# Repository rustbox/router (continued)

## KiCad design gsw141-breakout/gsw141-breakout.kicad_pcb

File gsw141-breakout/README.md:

# GSW141 Switch Chip Breakout

## Different Arrangements of the GSW141 Breakout PCB?

### RJ45 Jacks

* Internal Magnetics | External Magnetics
* LEDs | No LEDs
* 1000 (or higher) Base-T
    * I think 1G capable means that there are 4 twisted pairs
* "Tab Up" | "Tab Down"
    * This means the tab on the cable. When tab is down, the cat-5 pins all in a row point "up",
and vise versa when tab is up.
    * The GSW141 chip routes traces best with "tab down"
    * "Tab up" + on the reverse side of the board is equivalent to "tab down"
* How many ports per part

### Internal Magnetics

Use `ARJM11C7-502-KB-EW2` on mouser
* Tab up, so would have to be placed on the reverse side of the PCB
* $3.09 @ 10

4x 1 unit = $12.36

=====================================================================

Use `TMJG26945AENL` on mouser, 1x2 port
* Tab down
* $11.34 per unit

2x 1 unit = $22.68

=====================================================================

Use `TMJG46945AENL` on mouser, 1x4 port
* Tab down
* $18.84 per unit

### External Magnetics

* Mouser `1149848` 4 port RJ45 w/ LEDs, $4.34 each
    * Tab up, so would have to be placed on PCB reverse side
* Mouser `LAN2VSOD48351C2` dual port magnetics chip, ~$2 each

1 @ 4.34 + 2 @ $2 = $8.34

====================================================================

* Mouser `1149854` 2 port RJ45 w/LEDs, $2.78 each
    * Tab up, reverse PCB side
* Mouser `LAN2VSOD48351C2` dual port magnetics chip, ~$2 each

2 @ 2.78 + 2 @ 2 = $9.56

# Board Questions
[ ] How should the 1000 Base T diff pairs be terminated into the magnetics?

# Board TODO

[x] 4 port RJ45 jack
[x] RJ45 LEDs
[x] Management Interface
    * SPI, etc
    * Pin headers
    [x] Strapping pins?
        * `206-125ST` on mouser
        * or `DS01C-254-L-09BE`
[x] GPIO Pins, header
[x] RGMII/SGMII over edge connctor
[x] RGMII/SGMII header
    [x] Remove these headers actually
[x] Power regulation, 3.3V, 1.1V
[x] Power jack (latching) and jack
    * Mouser `T6634ST` barrel connector
    * 5.5 mm (out) x 2.1 mm (in)
    * Out 0v, inside, pos
    * Barrel Jack: `694106301002` for above
[x] Clock input
    * `ECS-400-12-33B2Q-JES-TR3` on mouser
    * Clock circuit cap calculation comes from https://blog.adafruit.com/2012/01/24/choosing-the-right-crystal-and-caps-for-your-design/
    * CL = C1 * C2 / (C1 + C2) + Cstray
    * Cstray is ~3 pF
    * If C1 = C2 = C, and CL = 12 pF for the above crystal
    * so C = 2(CL - Cstray) => C = 18 pF
[x] Power switch, latching
    * Digikey `PB400EEQR1BLK` maybe?
[x] Reset Button
    * button `TS21-34-035-BK-160-SMT-TR` on mouser
[ ] Power indicator LEDs
[x] GSW Power Startup sequence
    * RC delay from 3.3 V into 1.1V enable
[ ] Make sure trace clearance is okay
[ ] Power off?
[x] Power Caps on GSW chip
[x] Blank R for RESREF and RCAL
[ ] Fix the RJ45 / magnetic pinout alignment so routing is easier
[ ] Diff Pairs that are off by more than 10s of mm should be length tuned
[ ] Empty Footprint for linear regulator(s)?
[ ] TI 1G checklist https://www.ti.com/lit/an/snla387/snla387.pdf?ts=1720391456901

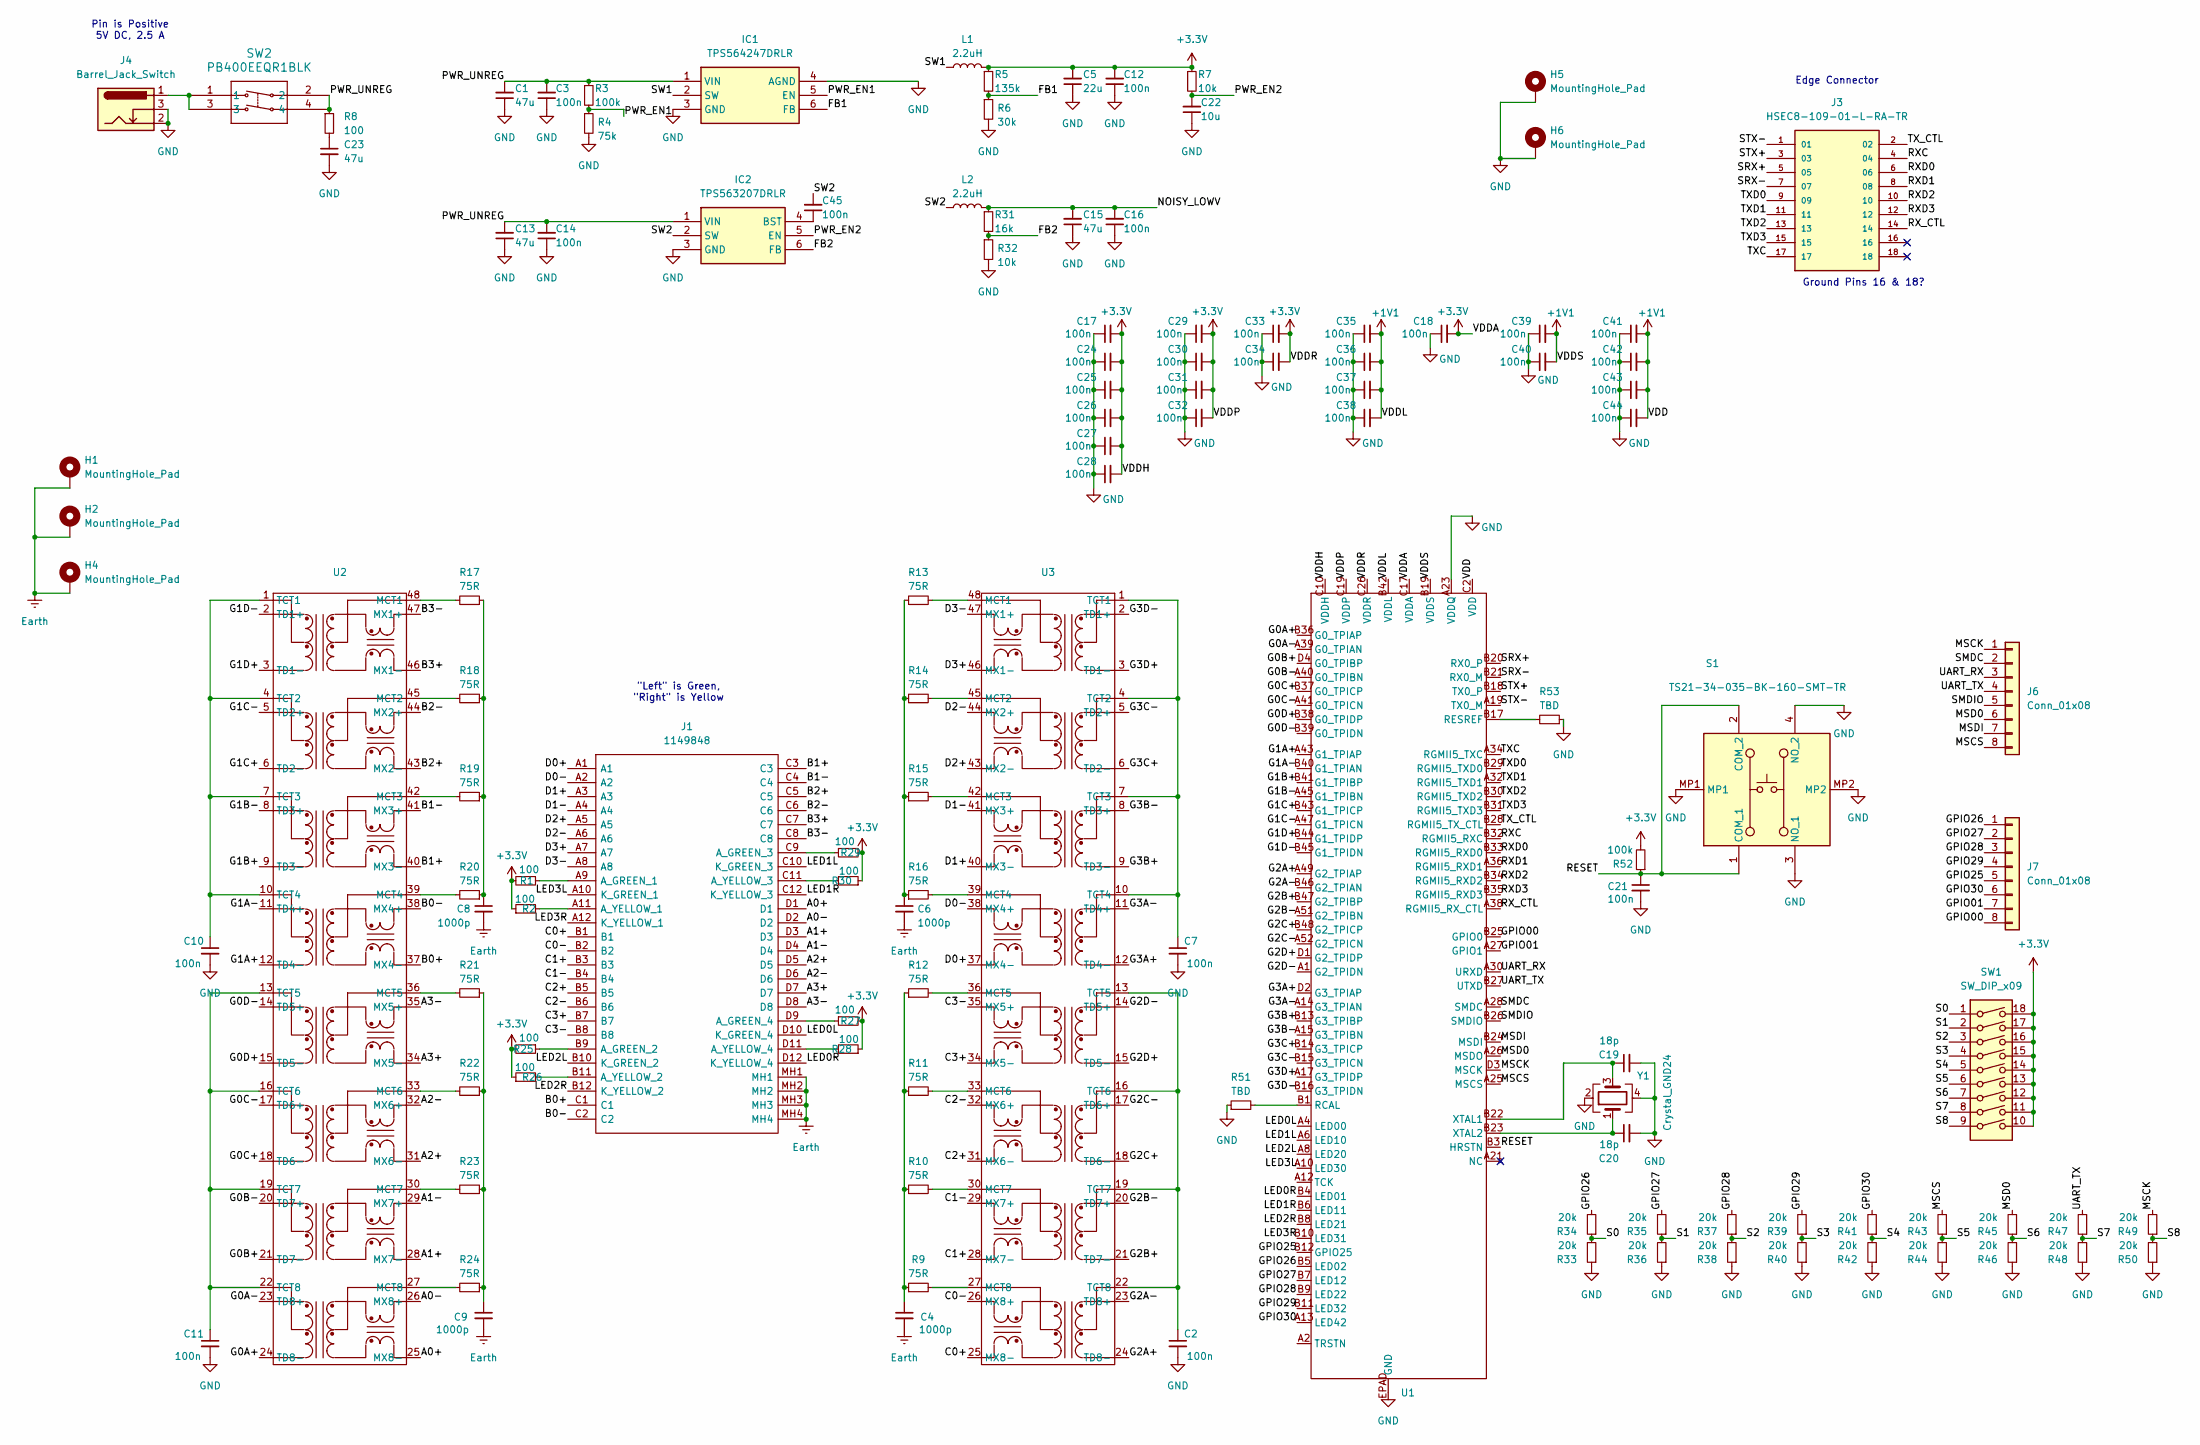
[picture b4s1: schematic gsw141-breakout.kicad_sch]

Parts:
C1, C13, C15, C23: 47u; C_0805_2012Metric_Pad1.18x1.45mm_HandSolder
C2, C3, C7, C10, C11, C12, C14, C16, C17, C18, C24, C25, C26, C27, C28, C29, C30, C31, C32, C33, C34, C35, C36, C37, C38, C39, C40, C41, C42, C43, C44, C45: 100n; C_0805_2012Metric_Pad1.18x1.45mm_HandSolder
C4, C6, C8, C9: 1000p; C_0805_2012Metric_Pad1.18x1.45mm_HandSolder
C5: 22u; C_0805_2012Metric_Pad1.18x1.45mm_HandSolder
C19, C20: 18p; C_0805_2012Metric
C21: 100n; C_0805_2012Metric
C22: 10u; C_0805_2012Metric_Pad1.18x1.45mm_HandSolder
H1, H2, H4, H5, H6: MountingHole_Pad; MountingHole_3.2mm_M3_Pad
IC1: TPS564247DRLR; SOTFL50P160X60-6N; Mouser Part Number 595-TPS564247DRLR
IC2: TPS563207DRLR; SOTFL50P160X60-6N; Mouser Part Number 595-TPS563207DRLR
J1: 1149848; Mouser Part Number 651-1149848
J3: HSEC8-109-01-L-RA-TR; Samtec_HSEC8-109-X-X-DV_2x09_P0.8mm_Edge; PARTREV Z
J4: Barrel_Jack_Switch; BarrelJack_Horizontal
J6, J7: Conn_01x08; PinHeader_1x08_P2.54mm_Vertical
L1, L2: 2.2uH; L_Abracon_ASPI-0425
R1, R2, R8, R25, R26, R27, R28, R29, R30: 100; R_0805_2012Metric_Pad1.20x1.40mm_HandSolder
R3, R52: 100k; R_0805_2012Metric_Pad1.20x1.40mm_HandSolder
R4: 75k; R_0805_2012Metric_Pad1.20x1.40mm_HandSolder
R5: 135k; R_0805_2012Metric_Pad1.20x1.40mm_HandSolder
R6: 30k; R_0805_2012Metric_Pad1.20x1.40mm_HandSolder
R7, R32: 10k; R_0805_2012Metric_Pad1.20x1.40mm_HandSolder
R9, R10, R11, R12, R13, R14, R15, R16, R17, R18, R19, R20, R21, R22, R23, R24: 75R; R_0805_2012Metric_Pad1.20x1.40mm_HandSolder
R31: 16k; R_0805_2012Metric_Pad1.20x1.40mm_HandSolder
R33, R34, R35, R36, R37, R38, R39, R40, R41, R42, R43, R44, R45, R46, R47, R48, R49, R50: 20k; R_0805_2012Metric_Pad1.20x1.40mm_HandSolder
R51, R53: TBD; R_0805_2012Metric_Pad1.20x1.40mm_HandSolder
S1: TS21-34-035-BK-160-SMT-TR; TS2134035BK160SMTTR; Mouser Part Number 179-134035BK160SMTTR
SW1: SW_DIP_x09; SW_DIP_SPSTx09_Slide_9.78x25.04mm_W7.62mm_P2.54mm
SW2: PB400EEQR1BLK; PB400EEQR1BLK_EWI
U1: XCVR_GSW140A3MC_S_LMHB
U2, U3: SMD-48
Y1: Crystal_GND24; Crystal_SMD_3225-4Pin_3.2x2.5mm_HandSoldering

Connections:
+1V1: C35.2, C36.2, C37.2, C38.2, C39.2, C40.2, C41.2, C42.2, C43.2, C44.2, U1.B19 (VDDS), U1.B42 (VDDL), U1.C2 (VDD), U1.C4 (VDD), U1.C12 (VDDL), U1.C15 (VDDS), U1.C23 (VDD), U1.C25 (VDD), U1.C33 (VDDL), U1.C37 (VDDL)
+3.3V: C5.2, C12.2, C17.2, C18.2, C24.2, C25.2, C26.2, C27.2, C28.2, C29.2, C30.2, C31.2, C32.2, C33.2, C34.2, L1.2, R1.2, R2.1, R5.1, R7.1, R25.2, R26.1, R27.2, R28.1, R29.2, R30.1, R52.2, SW1.10, SW1.11, SW1.12, SW1.13, SW1.14, SW1.15, SW1.16, SW1.17, SW1.18, U1.C6 (VDDP), U1.C8 (VDDP), U1.C10 (VDDH), U1.C14 (VDDH), U1.C17 (VDDA), U1.C19 (VDDP), U1.C21 (VDDP), U1.C26 (VDDR), U1.C28 (VDDR), U1.C31 (VDDH), U1.C34 (VDDH), U1.C36 (VDDH), U1.C39 (VDDH)
/A0+: J1.D1, U2.25 (MX8-)
/A0-: J1.D2, U2.26 (MX8+)
/A1+: J1.D3, U2.28 (MX7-)
/A1-: J1.D4, U2.29 (MX7+)
/A2+: J1.D5, U2.31 (MX6-)
/A2-: J1.D6, U2.32 (MX6+)
/A3+: J1.D7, U2.34 (MX5-)
/A3-: J1.D8, U2.35 (MX5+)
/B0+: J1.C1, U2.37 (MX4-)
/B0-: J1.C2, U2.38 (MX4+)
/B1+: J1.C3, U2.40 (MX3-)
/B1-: J1.C4, U2.41 (MX3+)
/B2+: J1.C5, U2.43 (MX2-)
/B2-: J1.C6, U2.44 (MX2+)
/B3+: J1.C7, U2.46 (MX1-)
/B3-: J1.C8, U2.47 (MX1+)
/C0+: J1.B1, U3.25 (MX8-)
/C0-: J1.B2, U3.26 (MX8+)
/C1+: J1.B3, U3.28 (MX7-)
/C1-: J1.B4, U3.29 (MX7+)
/C2+: J1.B5, U3.31 (MX6-)
/C2-: J1.B6, U3.32 (MX6+)
/C3+: J1.B7, U3.34 (MX5-)
/C3-: J1.B8, U3.35 (MX5+)
/D0+: J1.A1, U3.37 (MX4-)
/D0-: J1.A2, U3.38 (MX4+)
/D1+: J1.A3, U3.40 (MX3-)
/D1-: J1.A4, U3.41 (MX3+)
/D2+: J1.A5, U3.43 (MX2-)
/D2-: J1.A6, U3.44 (MX2+)
/D3+: J1.A7, U3.46 (MX1-)
/D3-: J1.A8, U3.47 (MX1+)
/FB1: IC1.6 (FB), R5.2, R6.1
/FB2: IC2.6 (FB), R31.2, R32.1
/G0A+: U1.B36 (G0_TPIAP), U2.24 (TD8-)
/G0A-: U1.A39 (G0_TPIAN), U2.23 (TD8+)
/G0B+: U1.D4 (G0_TPIBP), U2.21 (TD7-)
/G0B-: U1.A40 (G0_TPIBN), U2.20 (TD7+)
/G0C+: U1.B37 (G0_TPICP), U2.18 (TD6-)
/G0C-: U1.A41 (G0_TPICN), U2.17 (TD6+)
/G0D+: U1.B38 (G0_TPIDP), U2.15 (TD5-)
/G0D-: U1.B39 (G0_TPIDN), U2.14 (TD5+)
/G1A+: U1.A43 (G1_TPIAP), U2.12 (TD4-)
/G1A-: U1.B40 (G1_TPIAN), U2.11 (TD4+)
/G1B+: U1.B41 (G1_TPIBP), U2.9 (TD3-)
/G1B-: U1.A45 (G1_TPIBN), U2.8 (TD3+)
/G1C+: U1.B43 (G1_TPICP), U2.6 (TD2-)
/G1C-: U1.A47 (G1_TPICN), U2.5 (TD2+)
/G1D+: U1.B44 (G1_TPIDP), U2.3 (TD1-)
/G1D-: U1.B45 (G1_TPIDN), U2.2 (TD1+)
/G2A+: U1.A49 (G2_TPIAP), U3.24 (TD8-)
/G2A-: U1.B46 (G2_TPIAN), U3.23 (TD8+)
/G2B+: U1.B47 (G2_TPIBP), U3.21 (TD7-)
/G2B-: U1.A51 (G2_TPIBN), U3.20 (TD7+)
/G2C+: U1.B48 (G2_TPICP), U3.18 (TD6-)
/G2C-: U1.A52 (G2_TPICN), U3.17 (TD6+)
/G2D+: U1.D1 (G2_TPIDP), U3.15 (TD5-)
/G2D-: U1.A1 (G2_TPIDN), U3.14 (TD5+)
/G3A+: U1.D2 (G3_TPIAP), U3.12 (TD4-)
/G3A-: U1.A14 (G3_TPIAN), U3.11 (TD4+)
/G3B+: U1.B13 (G3_TPIBP), U3.9 (TD3-)
/G3B-: U1.A15 (G3_TPIBN), U3.8 (TD3+)
/G3C+: U1.B14 (G3_TPICP), U3.6 (TD2-)
/G3C-: U1.B15 (G3_TPICN), U3.5 (TD2+)
/G3D+: U1.A17 (G3_TPIDP), U3.3 (TD1-)
/G3D-: U1.B16 (G3_TPIDN), U3.2 (TD1+)
/GPIO00: J7.8, U1.B25 (GPIO0)
/GPIO01: J7.7, U1.A27 (GPIO1)
/GPIO25: J7.5, U1.B12 (GPIO25)
/GPIO26: J7.1, R34.2, U1.B5 (LED02)
/GPIO27: J7.2, R35.2, U1.B7 (LED12)
/GPIO28: J7.3, R37.2, U1.B9 (LED22)
/GPIO29: J7.4, R39.2, U1.B11 (LED32)
/GPIO30: J7.6, R41.2, U1.A13 (LED42)
/LED0L: J1.D10 (K_GREEN_4), U1.A4 (LED00)
/LED0R: J1.D12 (K_YELLOW_4), U1.B4 (LED01)
/LED1L: J1.C10 (K_GREEN_3), U1.A6 (LED10)
/LED1R: J1.C12 (K_YELLOW_3), U1.B6 (LED11)
/LED2L: J1.B10 (K_GREEN_2), U1.A8 (LED20)
/LED2R: J1.B12 (K_YELLOW_2), U1.B8 (LED21)
/LED3L: J1.A10 (K_GREEN_1), U1.A10 (LED30)
/LED3R: J1.A12 (K_YELLOW_1), U1.B10 (LED31)
/MSCK: J6.1, R49.2, U1.D3 (MSCK)
/MSCS: J6.8, R43.2, U1.A25 (MSCS)
/MSD0: J6.6, R45.2, U1.A26 (MSDO)
/MSDI: J6.7, U1.B24 (MSDI)
/NOISY_LOWV: C15.2, C16.2, L2.2, R31.1
/PWR_EN1: IC1.5 (EN), R3.2, R4.1
/PWR_EN2: C22.2, IC2.5 (EN), R7.2
/PWR_UNREG: C1.2, C3.2, C13.2, C14.2, IC1.1 (VIN), IC2.1 (VIN), R3.1, R8.1, SW2.2, SW2.4
/RESET: C21.1, R52.1, S1.1 (COM_1), S1.2 (COM_2), U1.B3 (HRSTN)
/RXC: J3.4, U1.B32 (RGMII5_RXC)
/RXD0: J3.6, U1.B33 (RGMII5_RXD0)
/RXD1: J3.8, U1.A36 (RGMII5_RXD1)
/RXD2: J3.10, U1.B34 (RGMII5_RXD2)
/RXD3: J3.12, U1.B35 (RGMII5_RXD3)
/RX_CTL: J3.14, U1.A38 (RGMII5_RX_CTL)
/S0: R33.2, R34.1, SW1.1
/S1: R35.1, R36.2, SW1.2
/S2: R37.1, R38.2, SW1.3
/S3: R39.1, R40.2, SW1.4
/S4: R41.1, R42.2, SW1.5
/S5: R43.1, R44.2, SW1.6
/S6: R45.1, R46.2, SW1.7
/S7: R47.1, R48.2, SW1.8
/S8: R49.1, R50.2, SW1.9
/SMDC: J6.2, U1.A28 (SMDC)
/SMDIO: J6.5, U1.B26 (SMDIO)
/SRX+: J3.5, U1.B20 (RX0_P)
/SRX-: J3.7, U1.B21 (RX0_M)
/STX+: J3.3, U1.B18 (TX0_P)
/STX-: J3.1, U1.A19 (TX0_M)
/SW1: IC1.2 (SW), L1.1
/SW2: C45.2, IC2.2 (SW), L2.1
/TXC: J3.17, U1.A34 (RGMII5_TXC)
/TXD0: J3.9, U1.B29 (RGMII5_TXD0)
/TXD1: J3.11, U1.A32 (RGMII5_TXD1)
/TXD2: J3.13, U1.B30 (RGMII5_TXD2)
/TXD3: J3.15, U1.B31 (RGMII5_TXD3)
/TX_CTL: J3.2, U1.B28 (RGMII5_TX_CTL)
/UART_RX: J6.3, U1.A30 (URXD)
/UART_TX: J6.4, R47.2, U1.B27 (UTXD)
Earth: C4.2, C6.2, C8.2, C9.2, H1.1, H2.1, H4.1, J1.MH1, J1.MH2, J1.MH3, J1.MH4
GND: C1.1, C2.2, C3.1, C5.1, C7.2, C10.2, C11.2, C12.1, C13.1, C14.1, C15.1, C16.1, C17.1, C18.1, C19.2, C20.2, C21.2, C22.1, C23.2, C24.1, C25.1, C26.1, C27.1, C28.1, C29.1, C30.1, C31.1, C32.1, C33.1, C34.1, C35.1, C36.1, C37.1, C38.1, C39.1, C40.1, C41.1, C42.1, C43.1, C44.1, H5.1, H6.1, IC1.3 (GND), IC1.4 (AGND), IC2.3 (GND), J4.2, J4.3, R4.2, R6.2, R32.2, R33.1, R36.1, R38.1, R40.1, R42.1, R44.1, R46.1, R48.1, R50.1, R51.1, R53.1, S1.3 (NO_1), S1.4 (NO_2), S1.MP1, S1.MP2, U1.A23 (VDDQ), U1.EPAD (GND), Y1.2, Y1.4
unnamed: C4.1, R9.1, R10.1, R11.1, R12.1
unnamed: C6.1, R13.1, R14.1, R15.1, R16.1
unnamed: C8.1, R17.1, R18.1, R19.1, R20.1
unnamed: C9.1, R21.1, R22.1, R23.1, R24.1
unnamed: C23.1, R8.2
unnamed: C45.1, IC2.4 (BST)
unnamed: J1.A9 (A_GREEN_1), R1.1
unnamed: J1.B9 (A_GREEN_2), R25.1
unnamed: J1.C9 (A_GREEN_3), R29.1
unnamed: J1.D9 (A_GREEN_4), R27.1
unnamed: J1.A11 (A_YELLOW_1), R2.2
unnamed: J1.B11 (A_YELLOW_2), R26.2
unnamed: J1.C11 (A_YELLOW_3), R30.2
unnamed: J1.D11 (A_YELLOW_4), R28.2
unnamed: J4.1, SW2.1, SW2.3
unnamed: R51.2, U1.B1 (RCAL)
unnamed: R53.2, U1.B17 (RESREF)
unnamed: C19.1, U1.B22 (XTAL1), Y1.3
unnamed: C20.1, U1.B23 (XTAL2), Y1.1
unnamed: R17.2, U2.48 (MCT1)
unnamed: R18.2, U2.45 (MCT2)
unnamed: R19.2, U2.42 (MCT3)
unnamed: R20.2, U2.39 (MCT4)
unnamed: R21.2, U2.36 (MCT5)
unnamed: R22.2, U2.33 (MCT6)
unnamed: R23.2, U2.30 (MCT7)
unnamed: R24.2, U2.27 (MCT8)
unnamed: C10.1, U2.1 (TCT1), U2.4 (TCT2), U2.7 (TCT3), U2.10 (TCT4)
unnamed: C11.1, U2.13 (TCT5), U2.16 (TCT6), U2.19 (TCT7), U2.22 (TCT8)
unnamed: R13.2, U3.48 (MCT1)
unnamed: R14.2, U3.45 (MCT2)
unnamed: R15.2, U3.42 (MCT3)
unnamed: R16.2, U3.39 (MCT4)
unnamed: R12.2, U3.36 (MCT5)
unnamed: R11.2, U3.33 (MCT6)
unnamed: R10.2, U3.30 (MCT7)
unnamed: R9.2, U3.27 (MCT8)
unnamed: C7.1, U3.1 (TCT1), U3.4 (TCT2), U3.7 (TCT3), U3.10 (TCT4)
unnamed: C2.1, U3.13 (TCT5), U3.16 (TCT6), U3.19 (TCT7), U3.22 (TCT8)

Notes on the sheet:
Ground Pins 16 & 18?
Edge Connector
Pin is Positive 5V DC, 2.5 A
"Left" is Green, "Right" is Yellow

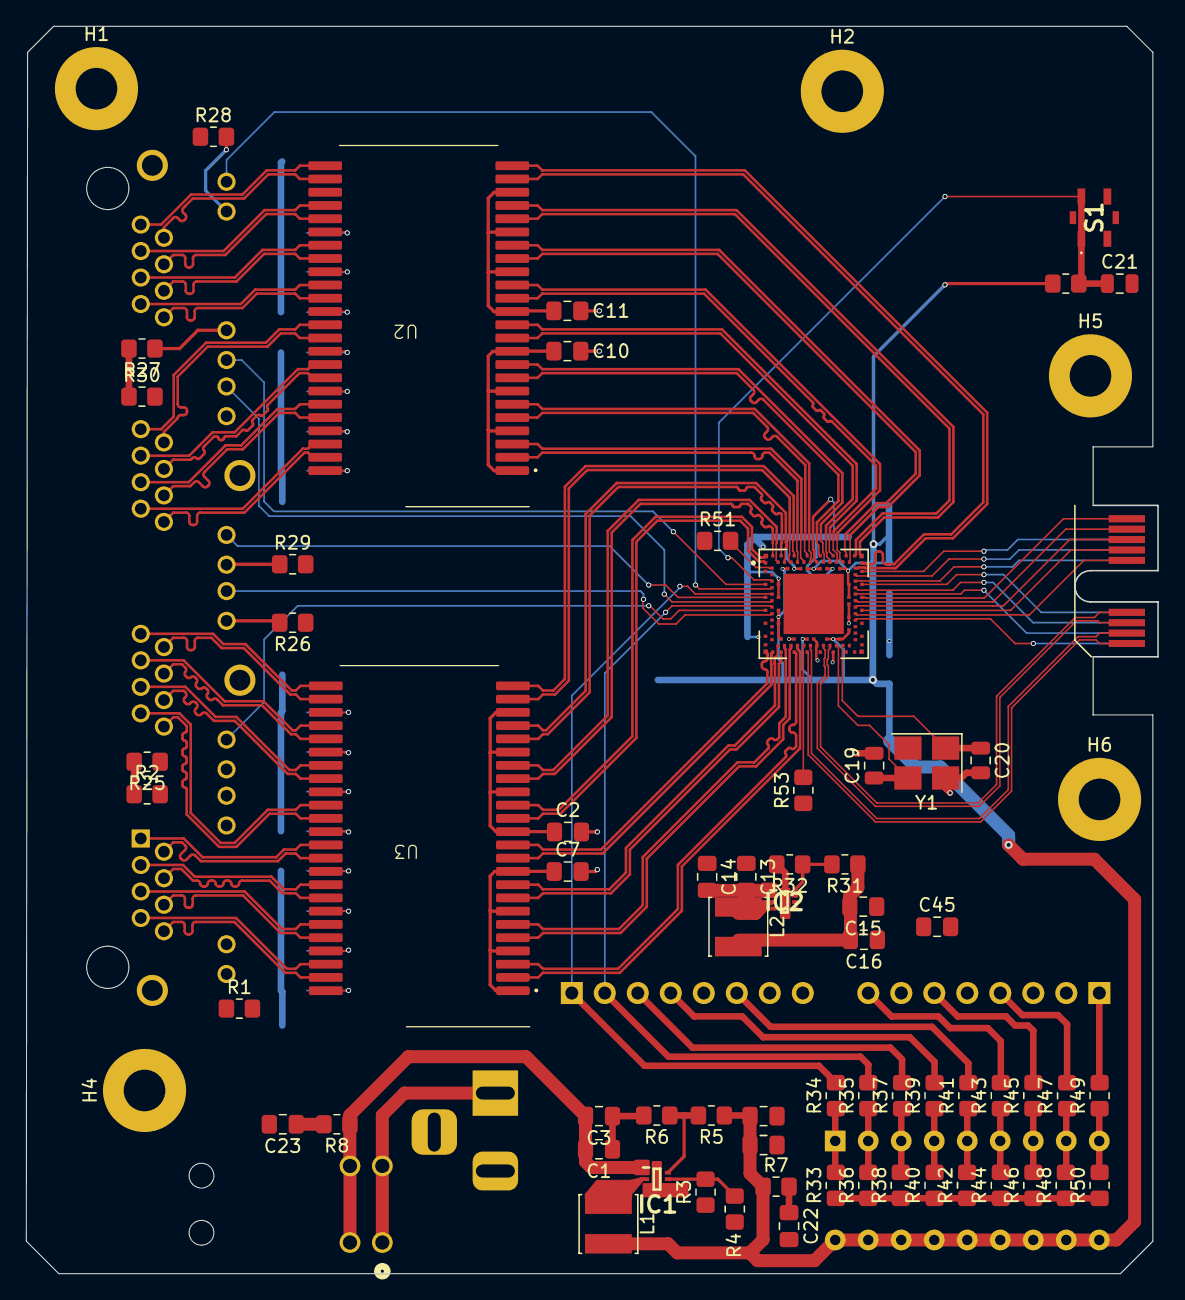
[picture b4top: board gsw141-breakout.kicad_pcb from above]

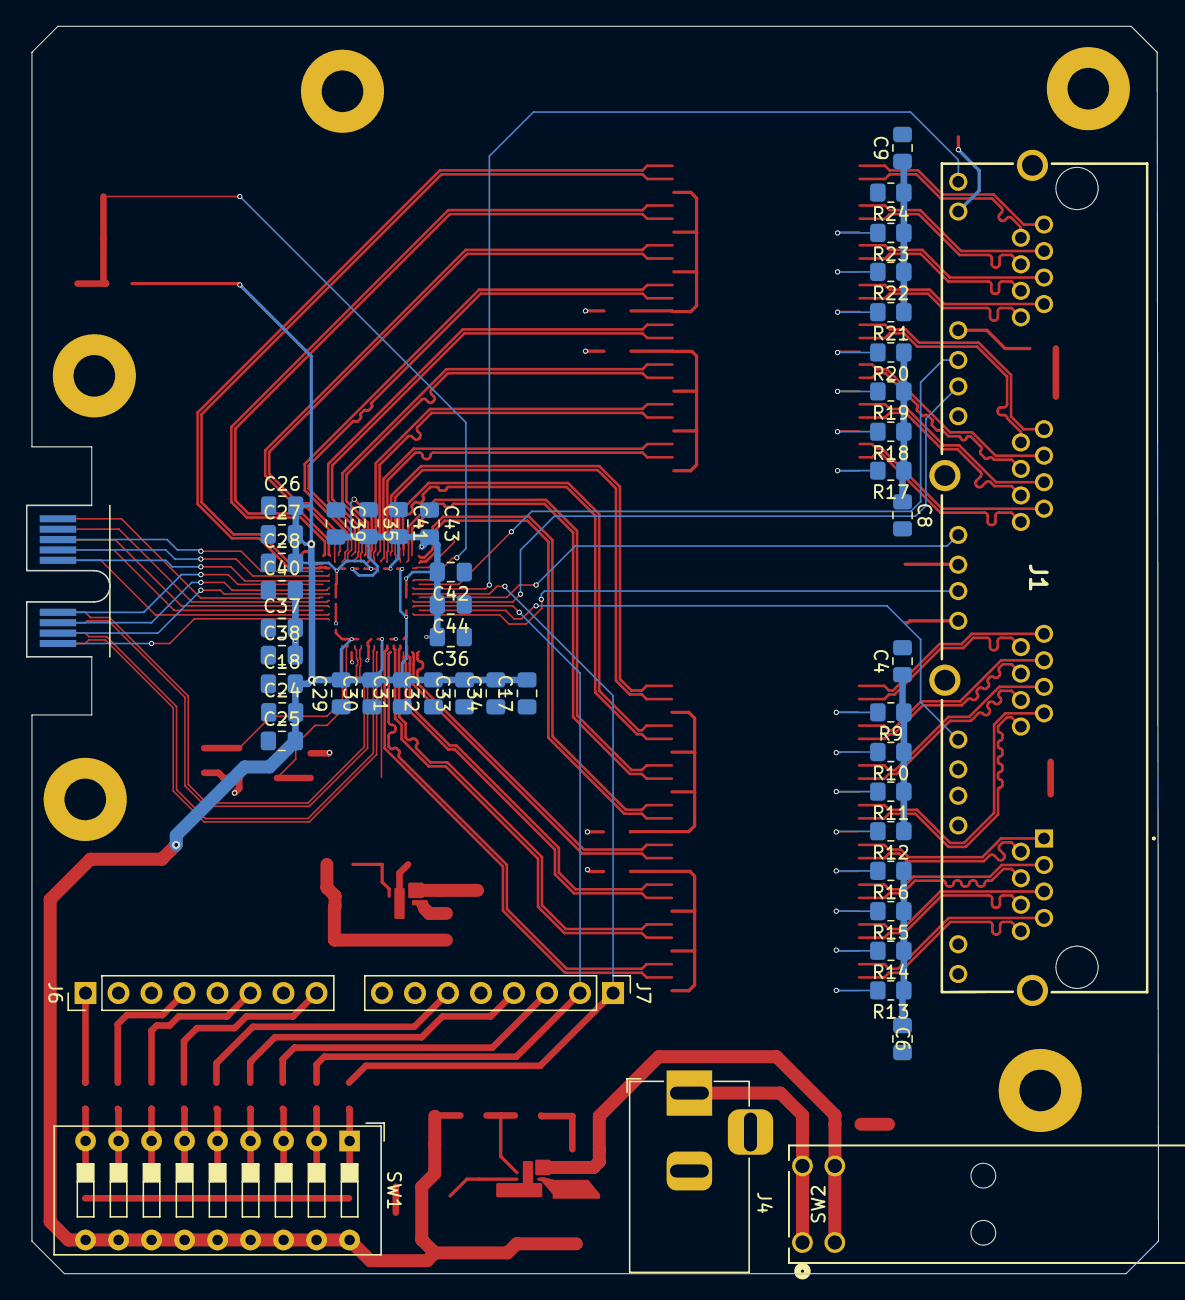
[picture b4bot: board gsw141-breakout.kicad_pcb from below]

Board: 4 copper layers, 87.1 x 95.9 mm, 119 parts (49 on the bottom side), 165 nets.

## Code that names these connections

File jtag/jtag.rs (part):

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    println!("Hello");
    println!("Clock: {}", &clocks.cpu_clock);

    let mdc = io.pins.gpio1;
    let mdio = io.pins.gpio0;

    let mut rstn = AnyOutputOpenDrain::new(io.pins.gpio2, Level::Low, Pull::Up);
    let mut reset = || {
        print!("resetting...");
        rstn.set_low();
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    let g = TimerGroup::new(peripherals.TIMG0, &clocks, None);
    let t = PeriodicTimer::new(ErasedTimer::Timg0Timer0(g.timer0));

    // let mut m = Mio::new(IOPin{pin: mdio}, OutPin{pin: mdc}, t);

    let status_reg = 0x02;

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
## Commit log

2024-07-10 init commit of existing gsw breakout kicad files and readme/todo list
2024-08-03 fixup: add kicad .gitignore, delete ignored bits
2024-08-03 feat: add tap example with a no_std pkt
    Porting this over from `pingd.py` in https://github.com/rustbox/discussion/discussions/3#discussioncomment-9334970
    Do be sure to run the setup commands first. Strange things might
    otherwise result.
2024-08-07 latest updates to the GSW breakout
2024-08-07 adding SYZYGY phy breakout board and schematic
2024-08-07 fixing diff pair skew from the twisted pair interface
2024-08-08 fixup: update kicad .gitignore, re-add Cargo.lock
2024-08-08 syzygy todo update
2024-08-08 wibbly wobbly
2024-08-09 more length tuning
2024-08-14 picking a concrete inductor and updating footprint, breakout out MDC/MDIO into headers instead of SYZYGY, corrected rules and text labels
2024-08-14 adding another mounting hole for a more stable 3 mounts
2024-08-14 adding GND stippling
2024-08-14 updating the caps and crystal, confirming the crystal circuit and footprints
2024-08-15 updating RGMII traces to be wider for 50 ohm target impedance and re-tuning lengths
2024-08-16 adding level shifter parts to schematic and pcb, rerouted RGMII and mostly length matched each channel
2024-08-16 adding power indicator LED
2024-08-16 adding footprint/symbol libraries I forgot earlier
2024-08-16 update 3d model paths to use variable
2024-08-16 fixing 3d model orientation
2024-08-16 misc changes + SYZYGY-PHY fixes
    fix up KiCad paths to be slightly friendlier to sharing between
    machines; assert that we only want to use the library from `../`
    relative so the 3d model path is valid.
    SYZYGY-PHY fixes:
    - add startup RC circuit to hold reset low for >1ms
    - add calibration resistors between PHY C+/- and GND
2024-08-16 fixed power lines, added keepout underneath RJ45, added ground stippling
2024-08-16 truly the Rx and Tx RGMII channels are length tuned very nearly exactly length tuned
2024-08-17 adding inductor footprint for 2016 metric sized inductor, and changed L1 footprint and added to the pcb, updated the schematic with the new inductor part and datasheet link
2024-08-17 do we like more text? Cant stop wont stop editing the board
2024-08-17 adding a GND header, adding 3.3V and 1.8V 1x2 header
2024-08-17 make DRC happier with a "solid" connection
    Instead of "thermal relief" where there isn't really room for it,
    connect to the zones by just allowing the fill to pour over the whole
    area.
2024-08-29 adding SYZYGY breakout board, ready for review
2024-08-29 adding some images
2024-08-29 forgot to add qsh symbol and model
2024-08-29 fixing length tuning
2024-08-30 four layer SYZYGY testing board that breaks out our pinouts for the RGMII interface which connects to the beagleV
2024-08-31 feat: add minimal jtag-over-esp32c3 skeleton
2024-08-31 feat: add dwf wrapper
2024-09-01 wip: start on some test notes
2024-09-02 adding top level readme
2024-09-04 syzygy phy docs
2024-09-05 updating gitignore and SYZYGY-PHY boards and footprints, and updating README with info on strapping pins and values
2024-09-06 board updates, length tuning again
2024-09-08 wip: set up three.js, board doesn't render
2024-09-08 wip: basic board render now working
2024-09-11 using jtag taps library to experiment with jtag communication
2024-09-12 wip: opt mode merging similar materials
2024-09-13 nfc: add some mouser numbers, quiet some warnings
    Also, updated the RJ45 jack's schematic symbol to show both LEDs in the
    left side.
    NFC=No Functional Changes
2024-09-13 mdio start
2024-09-14 Update TEST.md: notes and results from first round of testing
2024-09-15 making the mdio do things to gpy
2024-09-15 Update TEST.md: suggest changing ethertype
2024-09-18 jtag/mdio code update I guess. increase hole width and clearance to fit with jlcpcb reqs
2024-09-19 feat: add noline to jtag.rs; tweak SYZYGY-PHY schematic
2024-09-19 feat: bare-bones mdio repl
2024-09-23 wip part 2
2024-09-26 added a setphy command to allow talking to different PHY addresses, added a detect command to read all the connected PHY addresses, and a status command to read what PHY we're set to connect to
2024-09-26 obviously put the phy address outside the loop so it doesn't get clobbered every command ooops
2024-09-26 wip: working reads, has reset, also is a mess
2024-09-30 reads/writes work on main, added a detect, help, status, and setphy command
2024-10-01 busted: backwards level shifter
    This snapshot updates the pin assignments such that our TX level shifter
    fails the ERC, and then fixes that by flipping it in the schematic.
    It also pulls all the updated details from the schematic into the
    layout, which does not pass the DRC.
2024-10-02 flipping the level shifter adding some labels
2024-10-03 mild board updates before ordering
2024-10-03 had to reposition the level shifter by 0.05 mm to the right to not have to buy a new stencil
2024-10-12 feat: handle terminal resizing
2024-10-14 adding commands: skew, count, and relink
2024-10-14 adding test command
